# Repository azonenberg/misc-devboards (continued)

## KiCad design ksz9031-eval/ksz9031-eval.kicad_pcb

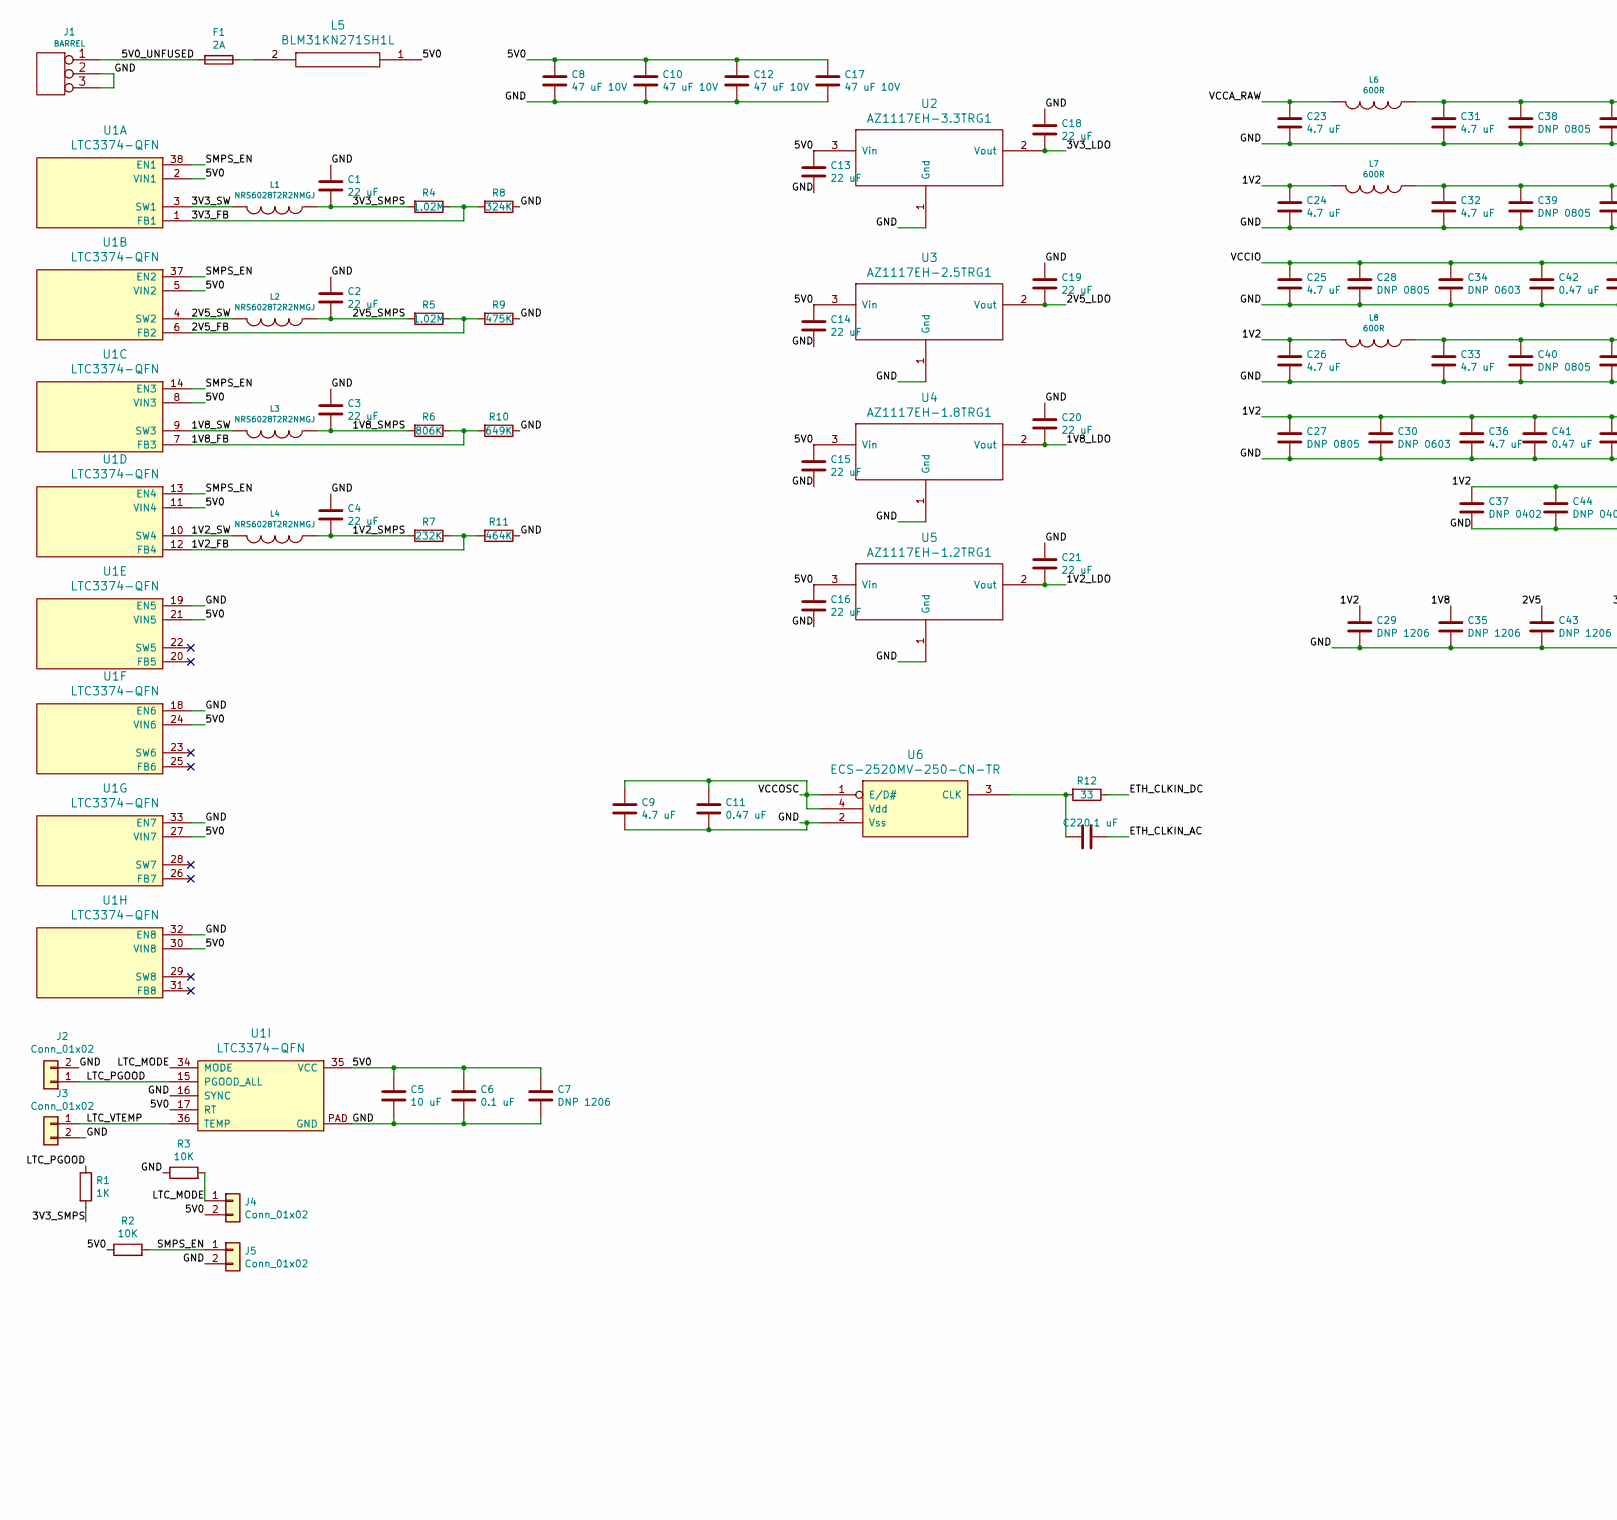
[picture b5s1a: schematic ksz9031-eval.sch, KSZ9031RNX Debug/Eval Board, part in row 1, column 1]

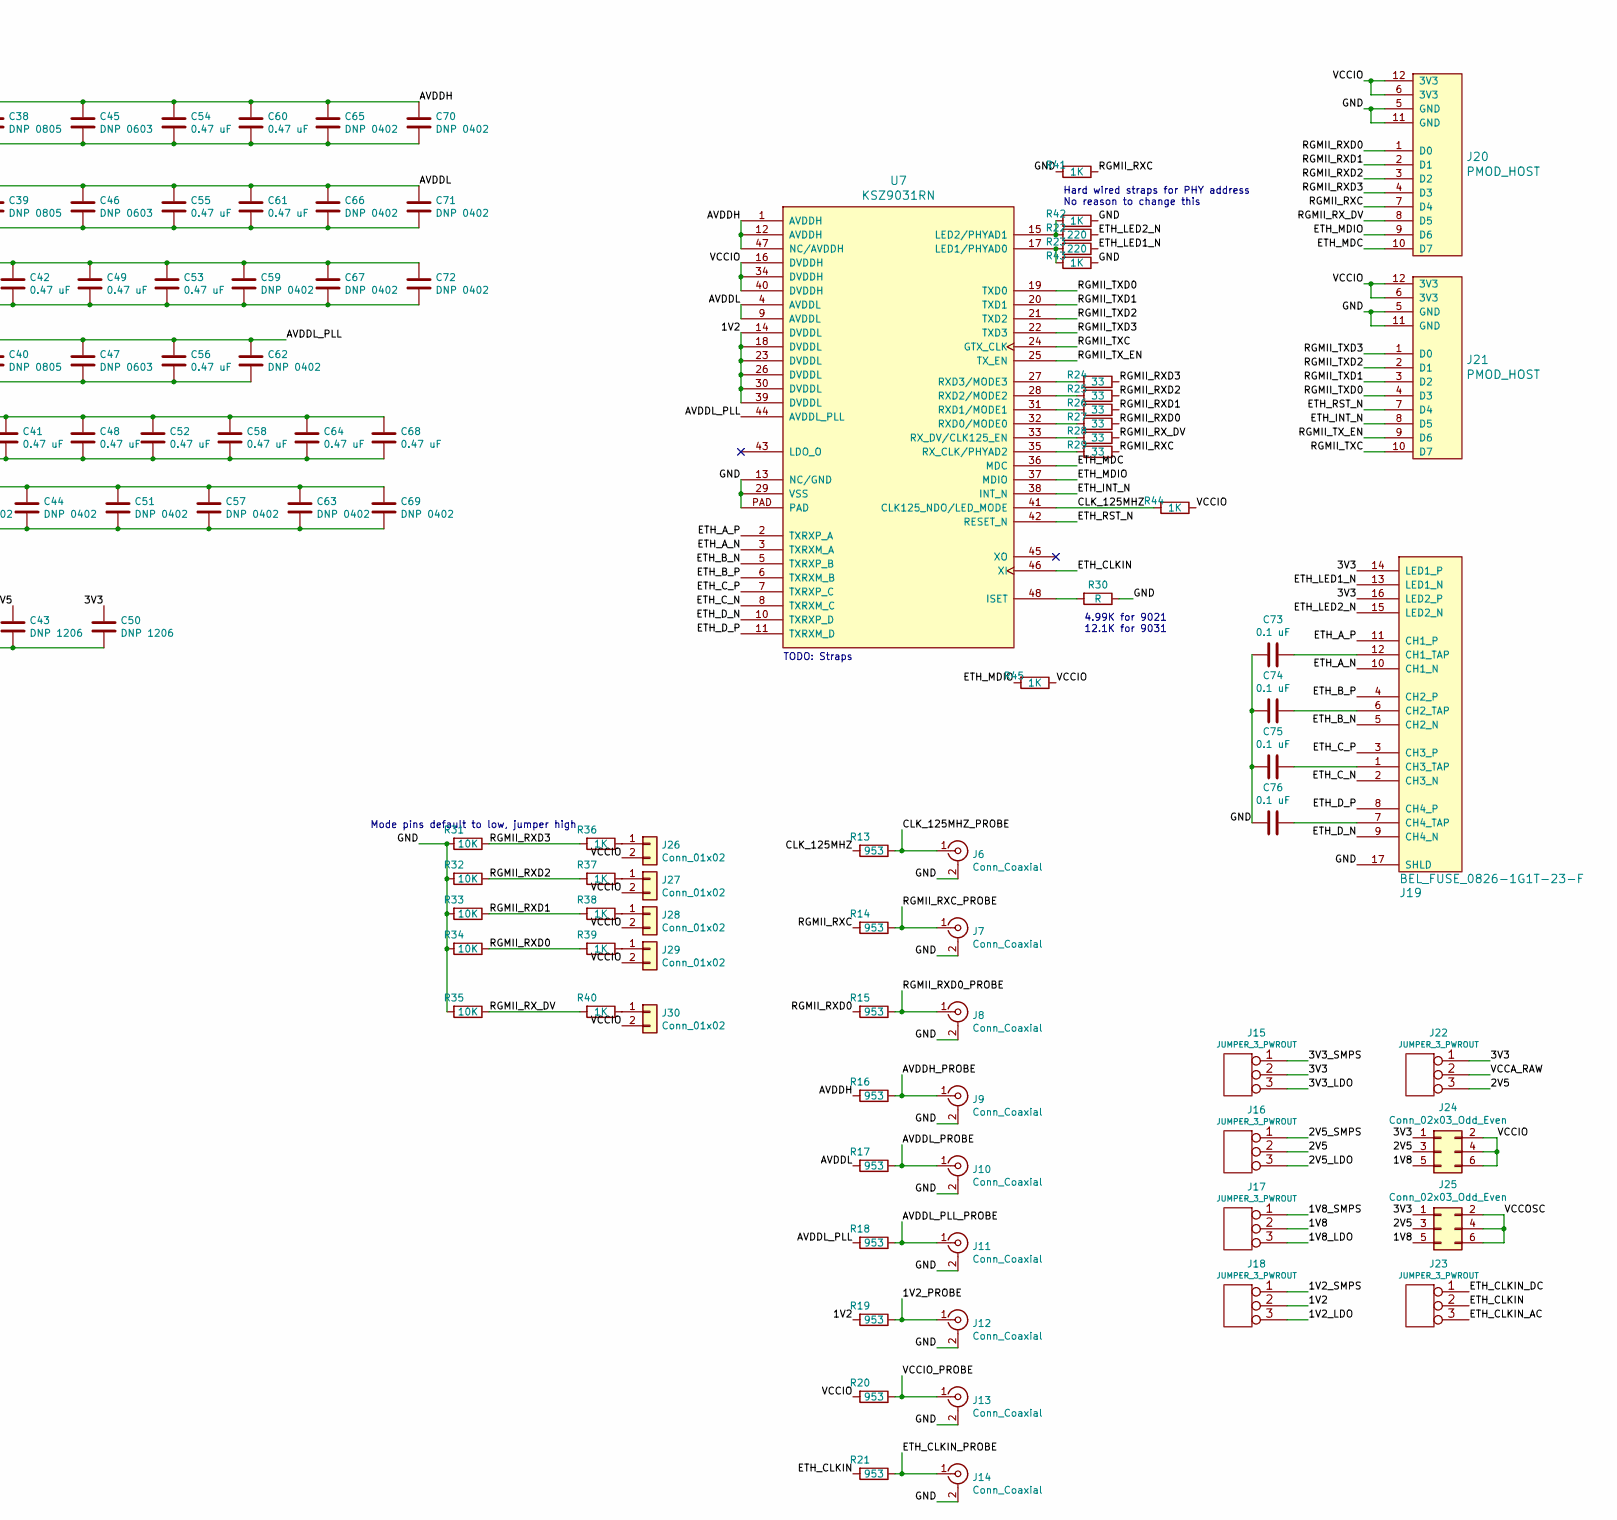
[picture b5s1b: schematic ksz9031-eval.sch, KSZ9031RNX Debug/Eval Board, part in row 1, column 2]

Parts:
C1, C2, C3, C4, C13, C14, C15, C16, C18, C19, C20, C21: 22 uF; EIA_1210_CAP_NOSILK
C5: 10 uF; EIA_1210_CAP_NOSILK
C6, C22, C73, C74, C75, C76: 0.1 uF; EIA_0402_CAP_NOSILK
C7, C29, C35, C43, C50: DNP 1206; EIA_1206_CAP_NOSILK
C8, C10, C12, C17: 47 uF 10V; EIA_1210_CAP_NOSILK
C9, C23, C24, C25, C26, C31, C32, C33, C36: 4.7 uF; EIA_0603_CAP_NOSILK
C11, C41, C42, C48, C49, C52, C53, C54, C55, C56, C58, C60, C61, C64, C68: 0.47 uF; EIA_0402_CAP_NOSILK
C27, C28, C38, C39, C40: DNP 0805; EIA_0805_CAP_NOSILK
C30, C34, C45, C46, C47: DNP 0603; EIA_0603_CAP_NOSILK
C37, C44, C51, C57, C59, C62, C63, C65, C66, C67, C69, C70, C71, C72: DNP 0402; EIA_0402_CAP_NOSILK
F1: 2A; EIA_0603_RES_NOSILK
J1: BARREL; CONN_CUI_PJ-058BH_HIPWR_BARREL_NOSLOT
J2, J3, J4, J5, J26, J27, J28, J29, J30: Conn_01x02; CONN_HEADER_2.54MM_1x2
J6, J7, J8, J9, J10, J11, J12, J13, J14: Conn_Coaxial; CONN_MMCX_LINX_CONNMMCX002SMD
J15, J16, J17, J18, J22, J23: JUMPER_3_PWROUT; CONN_HEADER_2.54MM_1x3
J19: BEL_FUSE_0826-1G1T-23-F; CONN_BELFUSE_0826_1G1T_23_F
J20, J21: PMOD_HOST; CONN_HEADER_2.54MM_2x6_RA_PMOD_HOST
J24, J25: Conn_02x03_Odd_Even; CONN_HEADER_2.54MM_2x3
L1, L2, L3, L4: NRS6028T2R2NMGJ; INDUCTOR_YUDEN_NR6028
L5: BLM31KN271SH1L; EIA_1206_CAP_NOSILK
L6, L7, L8: 600R; EIA_0402_RES_NOSILK
R1, R36, R37, R38, R39, R40, R41, R42, R43, R44, R45: 1K; EIA_0402_RES_NOSILK
R2, R3, R31, R32, R33, R34, R35: 10K; EIA_0402_RES_NOSILK
R4, R5: 1.02M; EIA_0402_RES_NOSILK
R6: 806K; EIA_0402_RES_NOSILK
R7: 232K; EIA_0402_RES_NOSILK
R8: 324K; EIA_0402_RES_NOSILK
R9: 475K; EIA_0402_RES_NOSILK
R10: 649K; EIA_0402_RES_NOSILK
R11: 464K; EIA_0402_RES_NOSILK
R12, R24, R25, R26, R27, R28, R29: 33; EIA_0402_RES_NOSILK
R13, R14, R15, R16, R17, R18, R19, R20, R21: 953; EIA_0402_RES_NOSILK
R22, R23: 220; EIA_0402_RES_NOSILK
R30: R; EIA_0402_RES_NOSILK
U1: LTC3374-QFN; QFN_38_0.5MM_5x7MM
U2: AZ1117EH-3.3TRG1; SOT223-4
U3: AZ1117EH-2.5TRG1; SOT223-4
U4: AZ1117EH-1.8TRG1; SOT223-4
U5: AZ1117EH-1.2TRG1; SOT223-4
U6: ECS-2520MV-250-CN-TR; OSCILLATOR_2.5x2.0
U7: KSZ9031RN; QFN_48_0.5MM_7x7MM

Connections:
/1V2: C24.1, C26.1, C27.1, C29.1, C30.1, C36.1, C37.1, C41.1, C44.1, C48.1, C51.1, C52.1, C57.1, C58.1, C63.1, C64.1, C68.1, C69.1, J18.2 (PM), L7.2, L8.2, R19.2, U7.14 (DVDDL), U7.18 (DVDDL), U7.23 (DVDDL), U7.26 (DVDDL), U7.30 (DVDDL), U7.39 (DVDDL)
/1V2_FB: R7.1, R11.2, U1.12 (FB4)
/1V2_LDO: C21.2, J18.3, U5.2 (Vout)
/1V2_PROBE: J12.1 (In), R19.1
/1V2_SMPS: C4.2, J18.1, L4.1, R7.2
/1V2_SW: L4.2, U1.10 (SW4)
/1V8: C35.1, J17.2 (PM), J24.5, J25.5
/1V8_FB: R6.1, R10.2, U1.7 (FB3)
/1V8_LDO: C20.2, J17.3, U4.2 (Vout)
/1V8_SMPS: C3.2, J17.1, L3.1, R6.2
/1V8_SW: L3.2, U1.9 (SW3)
/2V5: C43.1, J16.2 (PM), J22.3, J24.3, J25.3
/2V5_FB: R5.1, R9.2, U1.6 (FB2)
/2V5_LDO: C19.2, J16.3, U3.2 (Vout)
/2V5_SMPS: C2.2, J16.1, L2.1, R5.2
/2V5_SW: L2.2, U1.4 (SW2)
/3V3: C50.1, J15.2 (PM), J19.14 (LED1_P), J19.16 (LED2_P), J22.1, J24.1, J25.1
/3V3_FB: R4.1, R8.2, U1.1 (FB1)
/3V3_LDO: C18.2, J15.3, U2.2 (Vout)
/3V3_SMPS: C1.2, J15.1, L1.1, R1.2, R4.2
/3V3_SW: L1.2, U1.3 (SW1)
/5V0: C5.1, C6.1, C7.1, C8.1, C10.1, C12.1, C13.1, C14.1, C15.1, C16.1, C17.1, J4.2, L5.1, R2.1, U1.2 (VIN1), U1.5 (VIN2), U1.8 (VIN3), U1.11 (VIN4), U1.17 (RT), U1.21 (VIN5), U1.24 (VIN6), U1.27 (VIN7), U1.30 (VIN8), U1.35 (VCC), U2.3 (Vin), U3.3 (Vin), U4.3 (Vin), U5.3 (Vin)
/5V0_UNFUSED: F1.2, J1.1
/AVDDH: C31.1, C38.1, C45.1, C54.1, C60.1, C65.1, C70.1, L6.1, R16.2, U7.1 (AVDDH), U7.12 (AVDDH), U7.47 (NC/AVDDH)
/AVDDH_PROBE: J9.1 (In), R16.1
/AVDDL: C32.1, C39.1, C46.1, C55.1, C61.1, C66.1, C71.1, L7.1, R17.2, U7.4 (AVDDL), U7.9 (AVDDL)
/AVDDL_PLL: C33.1, C40.1, C47.1, C56.1, C62.1, L8.1, R18.2, U7.44 (AVDDL_PLL)
/AVDDL_PLL_PROBE: J11.1 (In), R18.1
/AVDDL_PROBE: J10.1 (In), R17.1
/CLK_125MHZ: R13.2, R44.2, U7.41 (CLK125_NDO/LED_MODE)
/CLK_125MHZ_PROBE: J6.1 (In), R13.1
/ETH_A_N: J19.10 (CH1_N), U7.3 (TXRXM_A)
/ETH_A_P: J19.11 (CH1_P), U7.2 (TXRXP_A)
/ETH_B_N: J19.5 (CH2_N), U7.5 (TXRXP_B)
/ETH_B_P: J19.4 (CH2_P), U7.6 (TXRXM_B)
/ETH_CLKIN: J23.2 (PM), R21.2, U7.46 (XI)
/ETH_CLKIN_AC: C22.1, J23.3
/ETH_CLKIN_DC: J23.1, R12.1
/ETH_CLKIN_PROBE: J14.1 (In), R21.1
/ETH_C_N: J19.2 (CH3_N), U7.8 (TXRXM_C)
/ETH_C_P: J19.3 (CH3_P), U7.7 (TXRXP_C)
/ETH_D_N: J19.9 (CH4_N), U7.10 (TXRXP_D)
/ETH_D_P: J19.8 (CH4_P), U7.11 (TXRXM_D)
/ETH_INT_N: J21.8 (D5), U7.38 (INT_N)
/ETH_LED1_N: J19.13 (LED1_N), R23.1
/ETH_LED2_N: J19.15 (LED2_N), R22.1
/ETH_MDC: J20.10 (D7), U7.36 (MDC)
/ETH_MDIO: J20.9 (D6), R45.2, U7.37 (MDIO)
/ETH_RST_N: J21.7 (D4), U7.42 (RESET_N)
/GND: C1.1, C2.1, C3.1, C4.1, C5.2, C6.2, C7.2, C8.2, C9.2, C10.2, C11.2, C12.2, C13.2, C14.2, C15.2, C16.2, C17.2, C18.1, C19.1, C20.1, C21.1, C23.2, C24.2, C25.2, C26.2, C27.2, C28.2, C29.2, C30.2, C31.2, C32.2, C33.2, C34.2, C35.2, C36.2, C37.2, C38.2, C39.2, C40.2, C41.2, C42.2, C43.2, C44.2, C45.2, C46.2, C47.2, C48.2, C49.2, C50.2, C51.2, C52.2, C53.2, C54.2, C55.2, C56.2, C57.2, C58.2, C59.2, C60.2, C61.2, C62.2, C63.2, C64.2, C65.2, C66.2, C67.2, C68.2, C69.2, C70.2, C71.2, C72.2, C73.2, C74.2, C75.2, C76.2, J1.2 (PM), J1.3, J2.2, J3.2, J5.2, J6.2 (Ext), J7.2 (Ext), J8.2 (Ext), J9.2 (Ext), J10.2 (Ext), J11.2 (Ext), J12.2 (Ext), J13.2 (Ext), J14.2 (Ext), J19.17 (SHLD), J20.5 (GND), J20.11 (GND), J21.5 (GND), J21.11 (GND), R3.1, R8.1, R9.1, R10.1, R11.1, R30.1, R31.2, R32.2, R33.2, R34.2, R35.2, R41.2, R42.1, R43.1, U1.16 (SYNC), U1.18 (EN6), U1.19 (EN5), U1.32 (EN8), U1.33 (EN7), U1.PAD (GND), U2.1 (Gnd), U3.1 (Gnd), U4.1 (Gnd), U5.1 (Gnd), U6.2 (Vss), U7.13 (NC/GND), U7.29 (VSS), U7.PAD
/LTC_MODE: J4.1, R3.2, U1.34 (MODE)
/LTC_PGOOD: J2.1, R1.1, U1.15 (PGOOD_ALL)
/LTC_VTEMP: J3.1, U1.36 (TEMP)
/RGMII_RXC: J20.7 (D4), R14.2, R29.1, R41.1
/RGMII_RXC_PROBE: J7.1 (In), R14.1
/RGMII_RXD0: J20.1 (D0), R15.2, R27.1, R34.1, R39.2
/RGMII_RXD0_PROBE: J8.1 (In), R15.1
/RGMII_RXD1: J20.2 (D1), R26.1, R33.1, R38.2
/RGMII_RXD2: J20.3 (D2), R25.1, R32.1, R37.2
/RGMII_RXD3: J20.4 (D3), R24.1, R31.1, R36.2
/RGMII_RX_DV: J20.8 (D5), R28.1, R35.1, R40.2
/RGMII_TXC: J21.10 (D7), U7.24 (GTX_CLK)
/RGMII_TXD0: J21.4 (D3), U7.19 (TXD0)
/RGMII_TXD1: J21.3 (D2), U7.20 (TXD1)
/RGMII_TXD2: J21.2 (D1), U7.21 (TXD2)
/RGMII_TXD3: J21.1 (D0), U7.22 (TXD3)
/RGMII_TX_EN: J21.9 (D6), U7.25 (TX_EN)
/SMPS_EN: J5.1, R2.2, U1.13 (EN4), U1.14 (EN3), U1.37 (EN2), U1.38 (EN1)
/VCCA_RAW: C23.1, J22.2 (PM), L6.2
/VCCIO: C25.1, C28.1, C34.1, C42.1, C49.1, C53.1, C59.1, C67.1, C72.1, J20.6 (3V3), J20.12 (3V3), J21.6 (3V3), J21.12 (3V3), J24.2, J24.4, J24.6, J26.2, J27.2, J28.2, J29.2, J30.2, R20.2, R44.1, R45.1, U7.16 (DVDDH), U7.34 (DVDDH), U7.40 (DVDDH)
/VCCIO_PROBE: J13.1 (In), R20.1
/VCCOSC: C9.1, C11.1, J25.2, J25.4, J25.6, U6.1 (E/D#), U6.4 (Vdd)
unnamed: C22.2, R12.2, U6.3 (CLK)
unnamed: C73.1, J19.12 (CH1_TAP)
unnamed: C74.1, J19.6 (CH2_TAP)
unnamed: C75.1, J19.1 (CH3_TAP)
unnamed: C76.1, J19.7 (CH4_TAP)
unnamed: F1.1, L5.2
unnamed: J26.1, R36.1
unnamed: J27.1, R37.1
unnamed: J28.1, R38.1
unnamed: J29.1, R39.1
unnamed: J30.1, R40.1
unnamed: R22.2, R42.2, U7.15 (LED2/PHYAD1)
unnamed: R23.2, R43.2, U7.17 (LED1/PHYAD0)
unnamed: R24.2, U7.27 (RXD3/MODE3)
unnamed: R25.2, U7.28 (RXD2/MODE2)
unnamed: R26.2, U7.31 (RXD1/MODE1)
unnamed: R27.2, U7.32 (RXD0/MODE0)
unnamed: R28.2, U7.33 (RX_DV/CLK125_EN)
unnamed: R29.2, U7.35 (RX_CLK/PHYAD2)
unnamed: R30.2, U7.48 (ISET)

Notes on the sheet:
TODO: Straps
4.99K for 9021 12.1K for 9031
Hard wired straps for PHY address No reason to change this
Mode pins default to low, jumper high

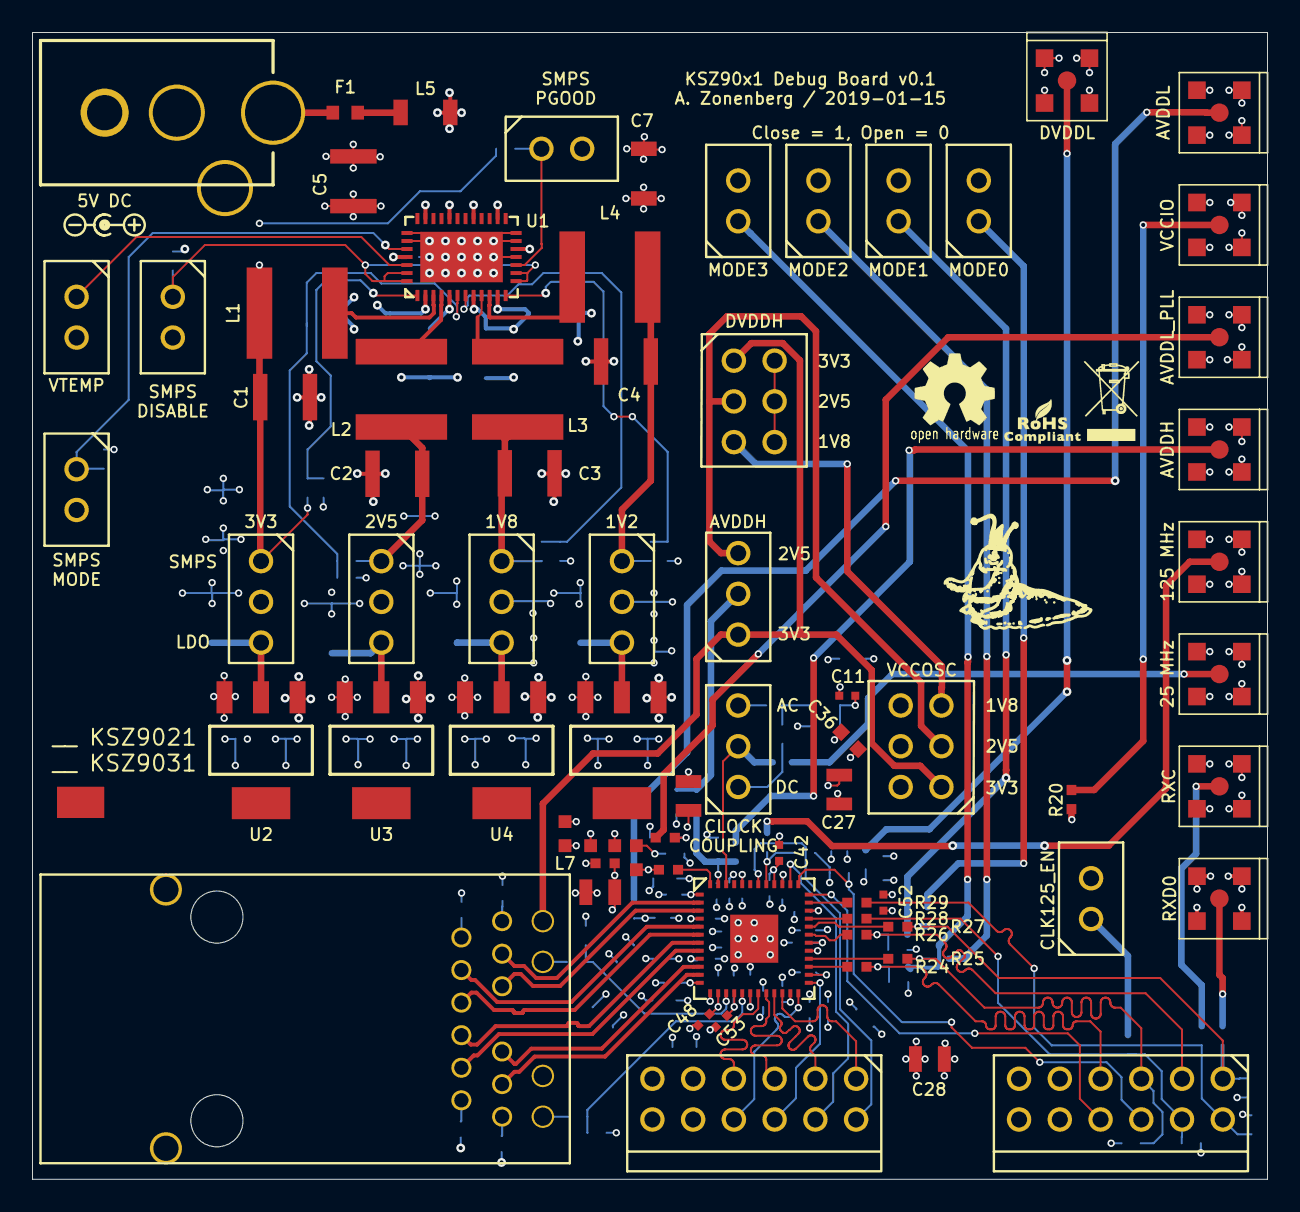
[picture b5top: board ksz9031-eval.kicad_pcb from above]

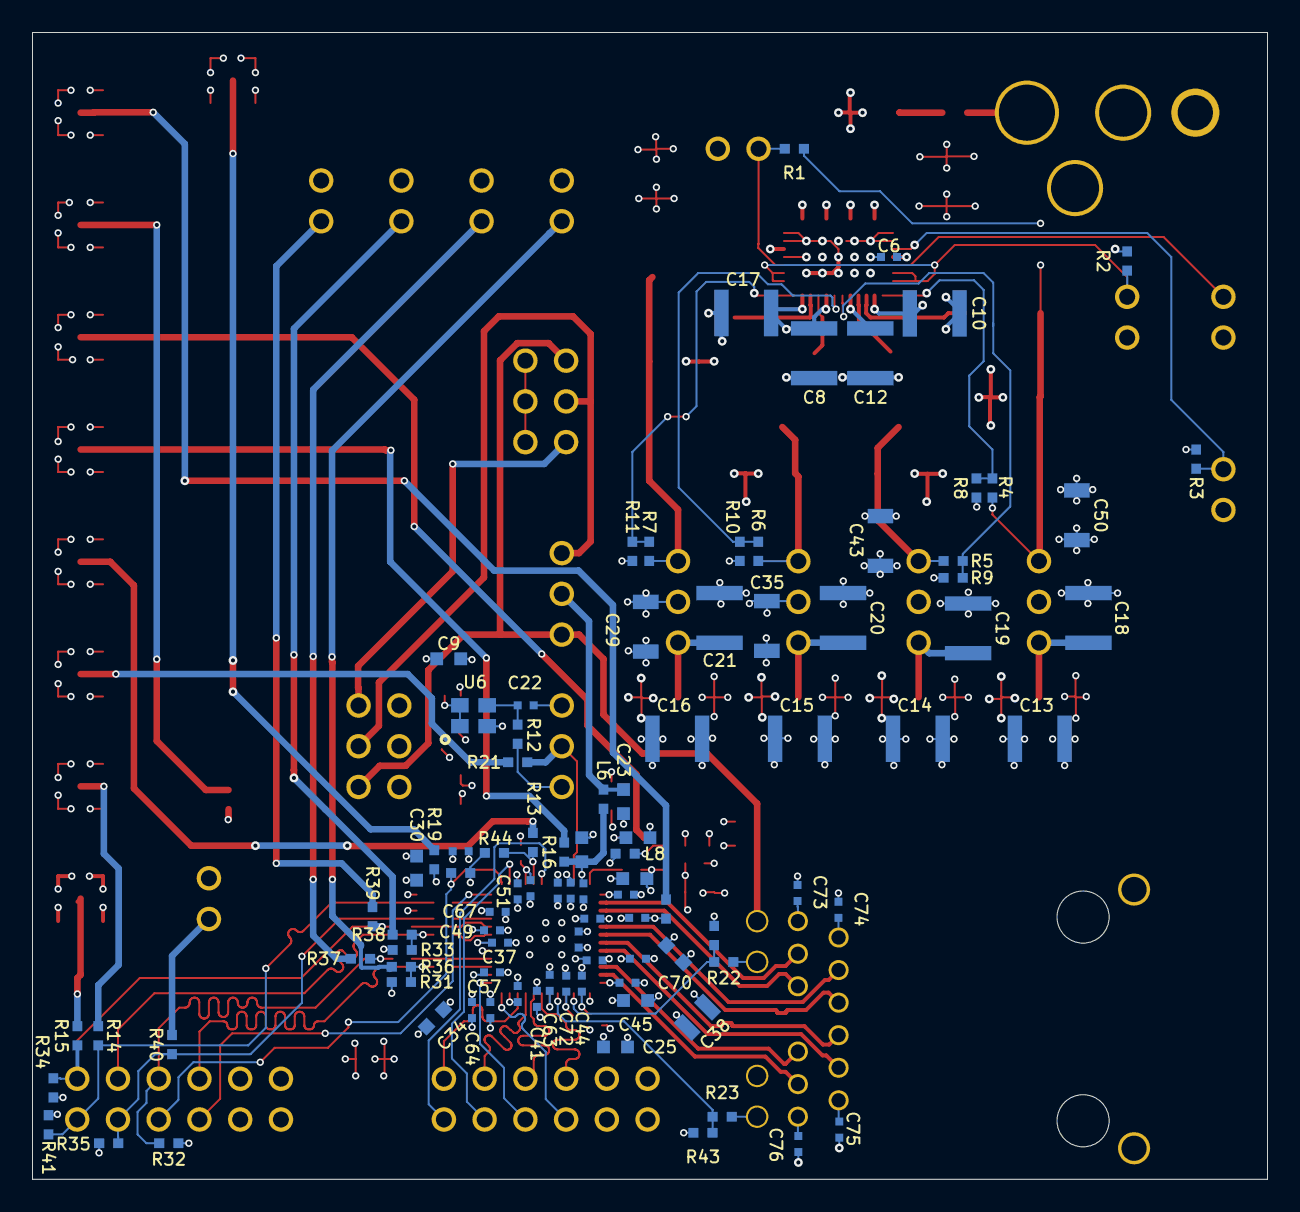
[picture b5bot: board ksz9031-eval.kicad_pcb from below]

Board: 4 copper layers, 77.0 x 71.5 mm, 167 parts (96 on the bottom side), 92 nets.

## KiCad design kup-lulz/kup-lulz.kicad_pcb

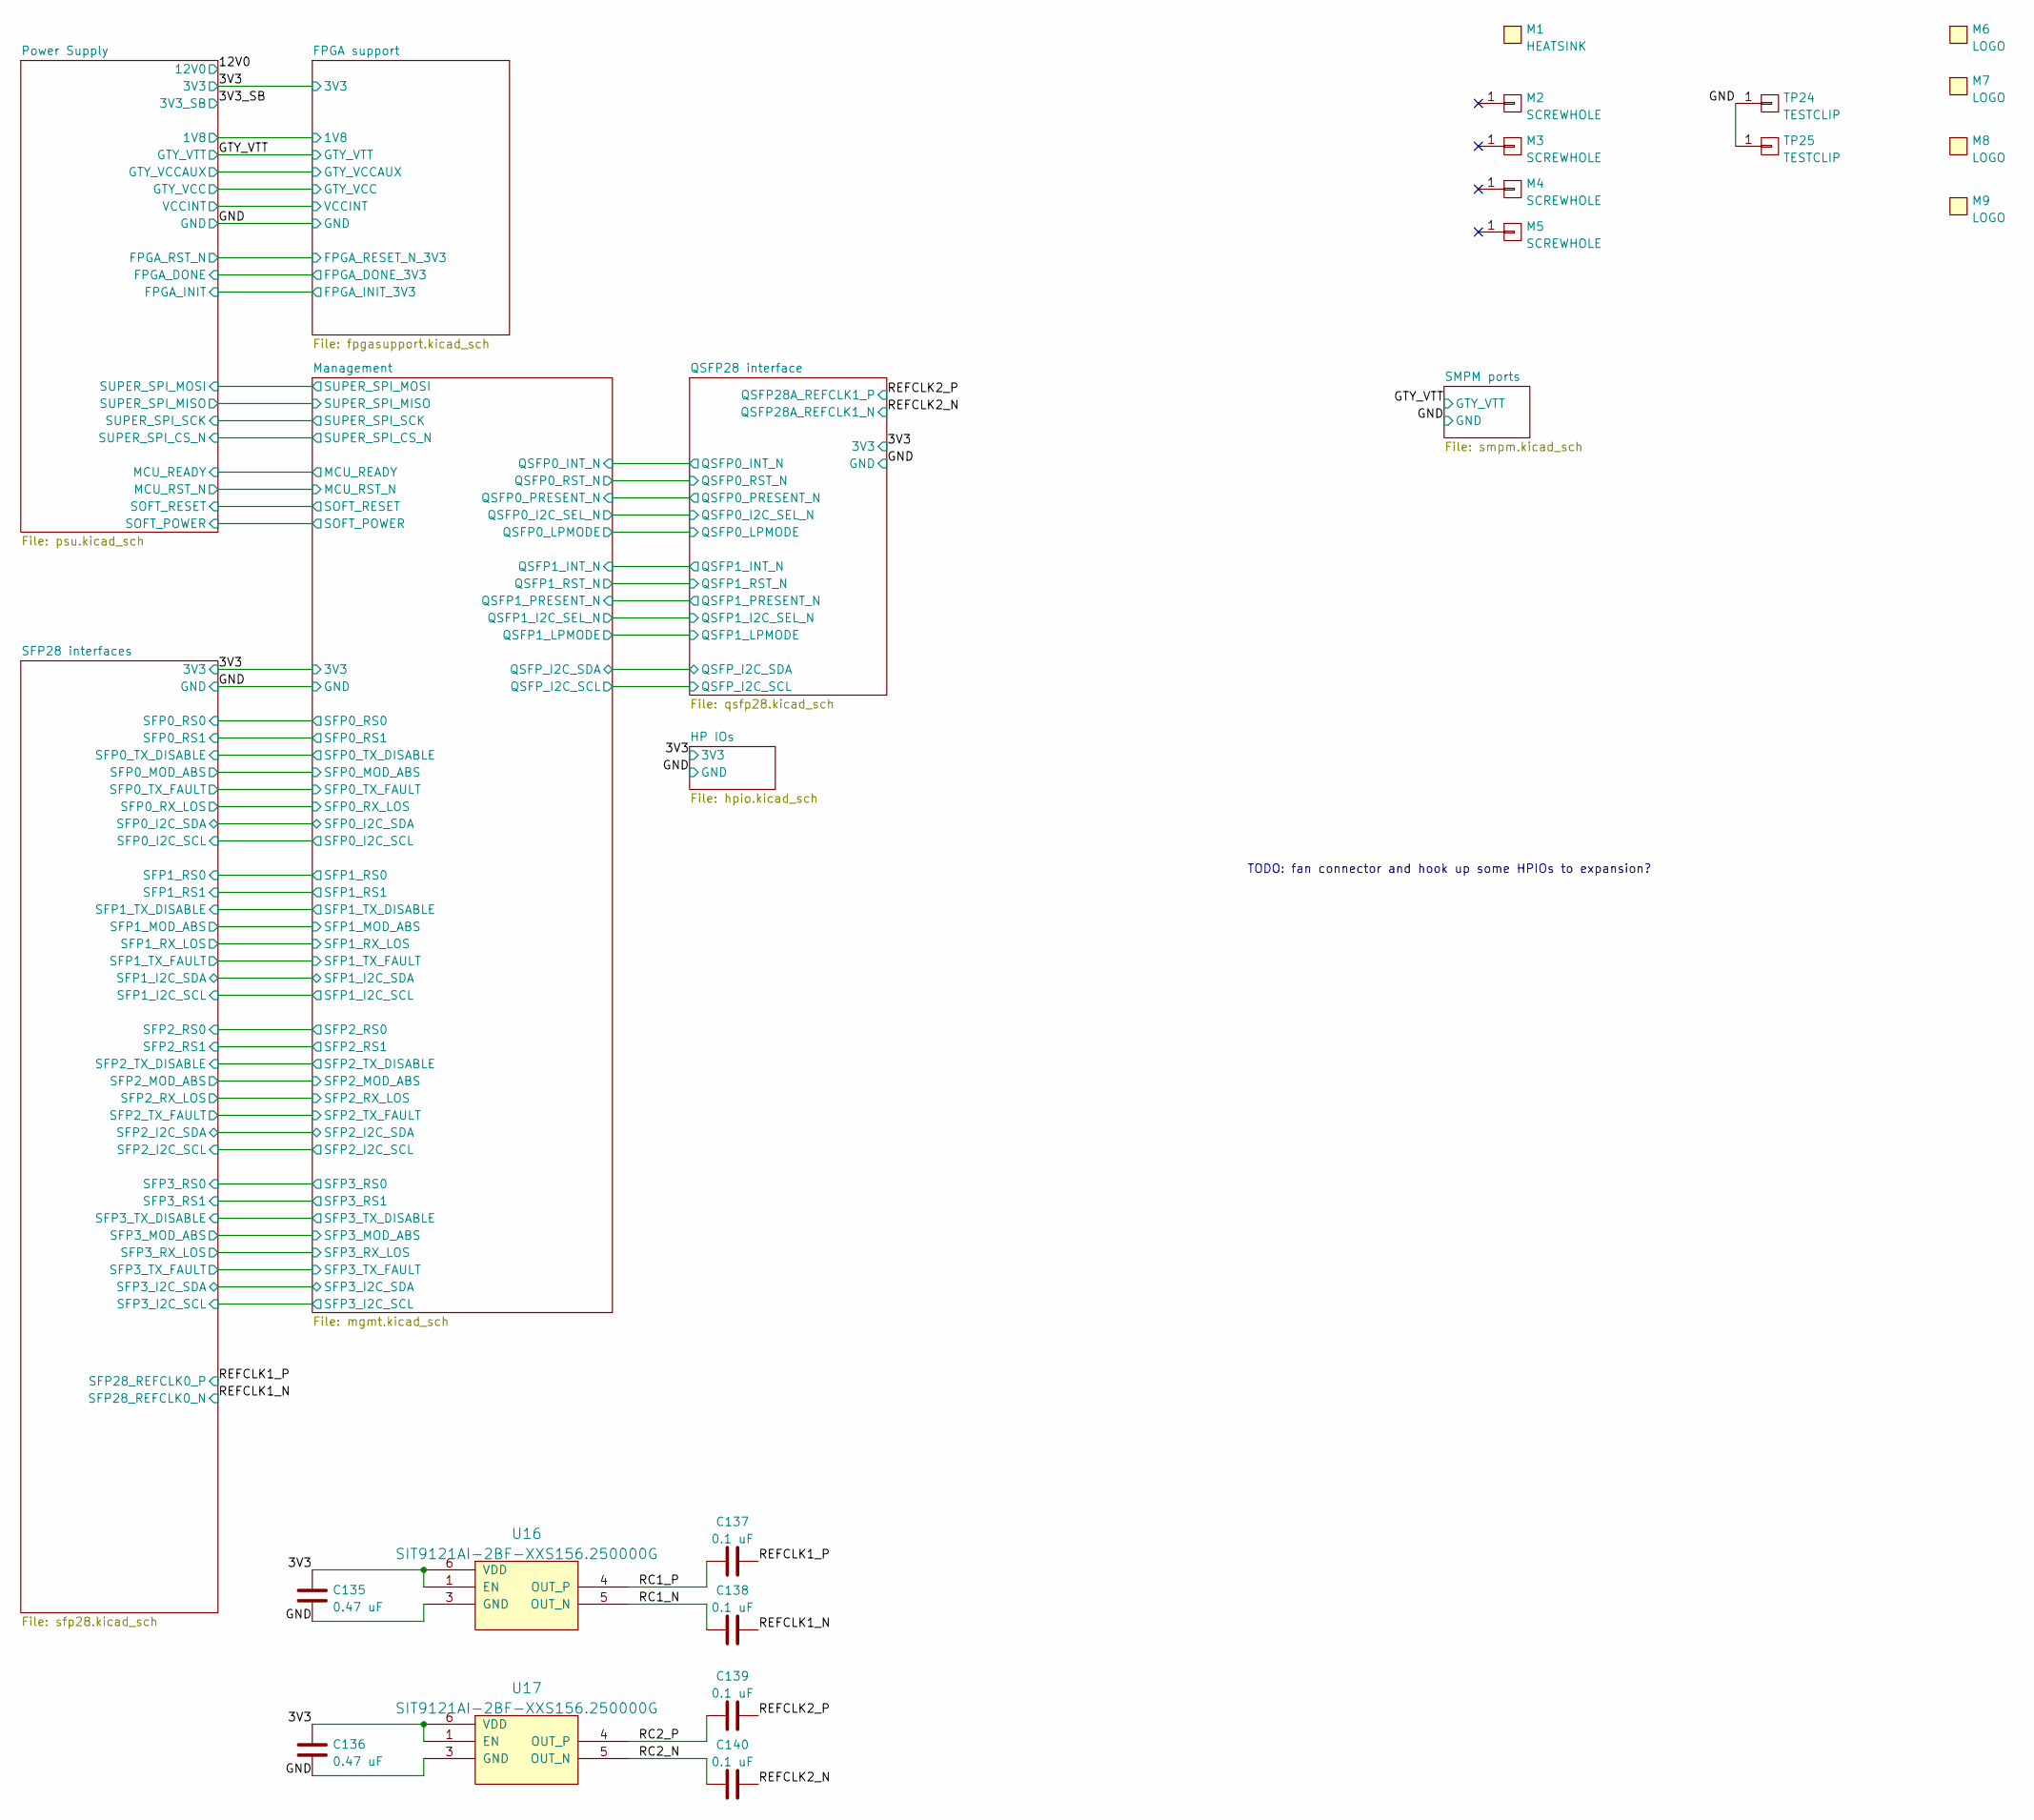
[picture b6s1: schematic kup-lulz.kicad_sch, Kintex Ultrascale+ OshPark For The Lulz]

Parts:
C135, C136: 0.47 uF; EIA_0402_CAP_NOSILK
C137, C138, C139, C140: 0.1 uF; EIA_0402_CAP_NOSILK
M1: HEATSINK; HEATSINK_WAKEFIELDVETTE_960-27-12-D-AB-0
M2, M3, M4, M5: SCREWHOLE; MECHANICAL_CLEARANCEHOLE_4_40
M6: LOGO; LONGTHING-1200DPI
M7: LOGO; Logo_silk_ROHS_5x2.8mm
M8: LOGO; Logo_silk_OSHW_6x6mm
M9: LOGO; Logo_silk_WEEE_3.4x5mm
TP24, TP25: TESTCLIP; TESTPOINT_SMT_KEYSTONE_5016
U16, U17: SIT9121AI-2BF-XXS156.250000G; OSCILLATOR_LVDS_3.2x2.5

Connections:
/3V3: C135.1, C136.1, U16.1 (EN), U16.6 (VDD), U17.1 (EN), U17.6 (VDD); also elsewhere on the board
/GND: C135.2, C136.2, TP24.1, TP25.1, U16.3 (GND), U17.3 (GND); also elsewhere on the board
/RC1_N: C138.1, U16.5 (OUT_N)
/RC1_P: C137.1, U16.4 (OUT_P)
/RC2_N: C140.1, U17.5 (OUT_N)
/RC2_P: C139.1, U17.4 (OUT_P)
/REFCLK1_N: C138.2; also elsewhere on the board
/REFCLK1_P: C137.2; also elsewhere on the board
/REFCLK2_N: C140.2; also elsewhere on the board
/REFCLK2_P: C139.2; also elsewhere on the board

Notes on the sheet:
TODO: fan connector and hook up some HPIOs to expansion?
